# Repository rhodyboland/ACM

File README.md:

# ACM V2
**Second generation of the ACM**

This device is intended to be a control module for accessories that have been fitted to a camping/touring/4wdriving oriented vehicle. These controllable accessories could be lighting, fridge, air commpressor, water pump, tv, and more. 
The device can take inputs from various sources and use internal logic to provide monitoring to the user.
The device is to be app controlled from a mobile phone.

### Hardware:
  - 3rd generation of custom PCB with high side switches from STM. Powered by ESP32-S3
    - STM High side switches with current sensing and auto disconnect
      - 2x VNQ9025AJTR Quad Channel 30A max
      - 1x VND9008AJTR Dual Channel 67A max
  - RGB LED WS2812B
  - ESP32-S3-WROOM1-N16R8
      - USB C Programming and debug
      - Reset and boot buttons
      - Auto selecting 12v or USB 5v 3v3 regulator
  - Inputs for 2 sensors and 2 12v switches/inputs
  - Outputs Term blocks
  - High current 12V input
  - CAN for expansion

### Software:
#### Platform IO using arduino framework
  - BLE
#### Features (configurable in app)
- Switches for each channel
- Battery voltage and percentage
- Total and individual current measurement
- Auto cut-out of outputs for low battery voltage with priority selection and auto cut-in
- Power used and remaining
- Victron VE Serial input and parsing (MPPT etc.)
- JK BMS input.
- Low side switched inverter control (Highside uses standard out)
- Diagnostic outputs
- CAN to esp32 display coming

#### Custom IOS App ####

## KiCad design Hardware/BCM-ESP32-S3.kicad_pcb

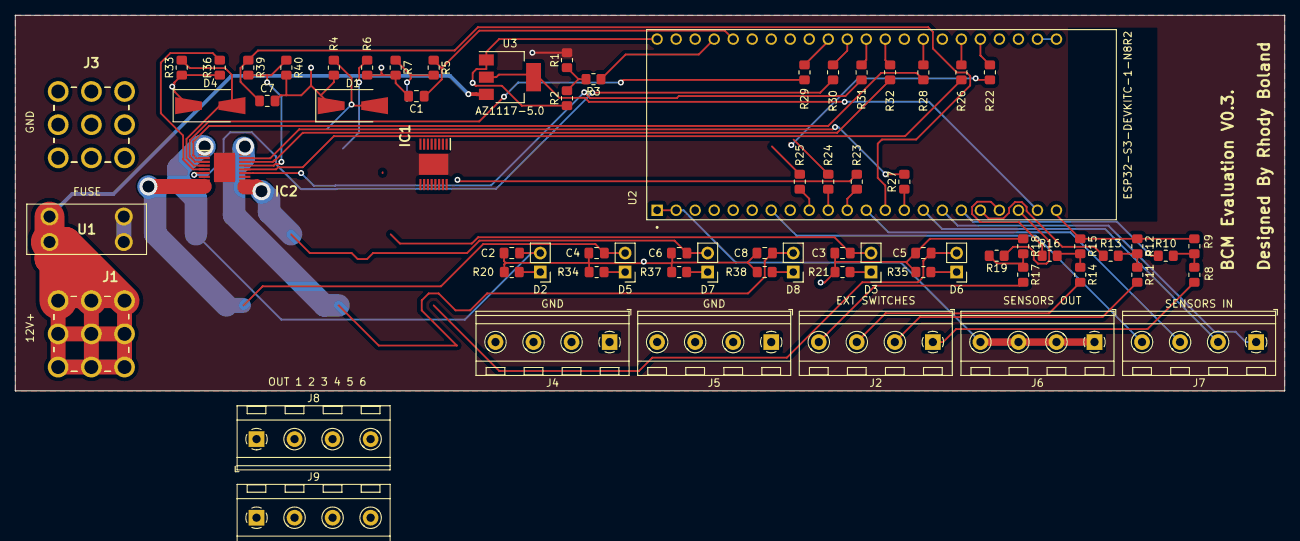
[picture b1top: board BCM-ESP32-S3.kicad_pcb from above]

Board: 2 copper layers, 169.5 x 50.2 mm, 70 parts (0 on the bottom side), 65 nets.

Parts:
C1, C2, C3, C4, C5, C6, C7, C8: 10nF; C_0805_2012Metric_Pad1.18x1.45mm_HandSolder
D1, D4: ES1DL; D_SMA-SMB_Universal_Handsoldering
D2, D3, D5, D6, D7, D8: LED; PinHeader_1x02_P2.54mm_Vertical
IC1: VND9012AJ; SOP50P600X170-17N
IC2: VNQ9080AJTR; SOP50P600X170-17N
J1: 12V+ Terminal; 74650194R
J2, J8, J9: EXT SWITCHES; TerminalBlock_RND_205-00234_1x04_P5.08mm_Horizontal
J3: GND Terminal; 74650194R
J4, J5: GND; TerminalBlock_RND_205-00234_1x04_P5.08mm_Horizontal
J6: SENSORS OUT; TerminalBlock_RND_205-00234_1x04_P5.08mm_Horizontal
J7: SENSORS IN; TerminalBlock_RND_205-00234_1x04_P5.08mm_Horizontal
R1, R5, R6, R8, R11, R14, R17, R22, R23, R24, R25, R26, R27, R28, R29, R30, R31, R32, R36, R39: 15K; R_0805_2012Metric_Pad1.20x1.40mm_HandSolder
R2, R4, R9, R12, R15, R18, R33: 4K7; R_0805_2012Metric_Pad1.20x1.40mm_HandSolder
R3, R7, R10, R13, R16, R19, R40: 1K; R_0805_2012Metric_Pad1.20x1.40mm_HandSolder
R20, R21, R34, R35, R37, R38: 2K2; R_0805_2012Metric_Pad1.20x1.40mm_HandSolder
U1: 3568
U2: ESP32-S3-DEVKITC-1-N8R2; XCVR_ESP32-S3-DEVKITC-1-N8R2
U3: AZ1117-5.0; SOT-223-3_TabPin2

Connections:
+3V3: J6.1, J6.2, J6.3, J6.4, U2.J1_1 (3V3), U2.J1_2 (3V3)
+5V: U2.J1_21 (5V0), U3.2 (VO)
+12V: IC1.17 (VCC), IC2.17 (VCC), R1.2, U1.3, U1.4
/Dual_CS: C1.1, R5.1, U2.J3_5 (GPIO2)
/Dual_INPUT0: IC1.1 (INPUT0), R25.2
/Dual_INPUT1: IC1.8 (INPUT1), R24.2
/Dual_SEL: IC1.5 (SEL), R23.2
/Dual_SEN: IC1.3 (SEn), R22.2
/EXT0: R10.1, U2.J1_17 (GPIO11)
/EXT1: R13.1, U2.J1_18 (GPIO12)
/EXT2: R16.1, U2.J1_19 (GPIO13)
/EXT3: R19.1, U2.J1_20 (GPIO14)
/EXT_SWITCH0: J2.1, R8.2
/EXT_SWITCH1: J2.2, R11.2
/EXT_SWITCH2: J2.3, R14.2
/EXT_SWITCH3: J2.4, R17.2
/OUT0: C2.1, D2.2 (A), IC2.1 (OUTPUT0), J8.1
/OUT1: C4.1, D5.2 (A), IC2.8 (OUTPUT1), J8.2
/OUT2: C6.1, D7.2 (A), IC2.9 (OUTPUT2), J8.3
/OUT3: C8.1, D8.2 (A), IC2.16 (OUTPUT3), J8.4
/OUT4: C3.1, D3.2 (A), IC1.13 (OUTPUT0), IC1.14 (OUTPUT0), IC1.15 (OUTPUT0), IC1.16 (OUTPUT0), J9.1
/OUT5: C5.1, D6.2 (A), IC1.9 (OUTPUT1), IC1.10 (OUTPUT1), IC1.11 (OUTPUT1), IC1.12 (OUTPUT1), J9.2
/Quad_CS: C7.1, R39.1, U2.J1_13 (GPIO3)
/Quad_INPUT0: IC2.3 (INPUT0), R29.2
/Quad_INPUT1: IC2.6 (INPUT1), R30.2
/Quad_INPUT2: IC2.11 (INPUT2), R31.2
/Quad_INPUT3: IC2.14 (INPUT3), R32.2
/Quad_SEL0: IC2.12 (SEL0), R26.2
/Quad_SEL1: IC2.15 (SEL1), R27.2
/Quad_SEN: IC2.2 (SEN), R28.2
/VBAT_ADC: R3.1, U2.J3_4 (GPIO1)
GND: C1.2, C2.2, C3.2, C4.2, C5.2, C6.2, C7.2, C8.2, D1.1 (K), D4.1 (K), J3.1, J3.2, J3.3, J3.4, J3.5, J3.6, J3.7, J3.8, J3.9, J4.1, J4.2, J4.3, J4.4, J5.1, J5.2, J5.3, J5.4, R2.1, R4.1, R6.1, R7.2, R9.1, R12.1, R15.1, R18.1, R20.1, R21.1, R33.1, R34.1, R35.1, R36.1, R37.1, R38.1, R40.2, U2.J1_22 (GND), U2.J3_1 (GND), U2.J3_21 (GND), U2.J3_22 (GND), U3.1 (GND)
unnamed: D1.2 (A), IC1.4 (GND), R4.2
unnamed: D2.1 (K), R20.2
unnamed: D3.1 (K), R21.2
unnamed: D4.2 (A), IC2.4 (GND), R33.2
unnamed: D5.1 (K), R34.2
unnamed: D6.1 (K), R35.2
unnamed: D7.1 (K), R37.2
unnamed: D8.1 (K), R38.2
unnamed: IC1.7 (CS), R5.2, R7.1
unnamed: IC1.2 (FaultRST), R6.2
unnamed: IC2.13 (CS), R39.2, R40.1
unnamed: IC2.5 (~FAULTRST), R36.2
unnamed: J7.1, U2.J1_16 (GPIO10)
unnamed: J7.2, U2.J1_15 (GPIO9)
unnamed: J7.3, U2.J1_12 (GPIO8)
unnamed: J7.4, U2.J1_7 (GPIO7)
unnamed: R1.1, R2.2, R3.2
unnamed: R8.1, R9.2, R10.2
unnamed: R11.1, R12.2, R13.2
unnamed: R14.1, R15.2, R16.2
unnamed: R17.1, R18.2, R19.2
unnamed: R25.1, U2.J1_9 (GPIO16)
unnamed: R24.1, U2.J1_10 (GPIO17)
unnamed: R23.1, U2.J1_11 (GPIO18)
unnamed: R22.1, U2.J3_18 (GPIO21)
unnamed: R32.1, U2.J3_13 (GPIO35)
unnamed: R31.1, U2.J3_12 (GPIO36)
unnamed: R30.1, U2.J3_11 (GPIO37)
unnamed: R29.1, U2.J3_10 (GPIO38)
unnamed: R28.1, U2.J3_15 (GPIO45)
unnamed: R27.1, U2.J1_14 (GPIO46)
unnamed: R26.1, U2.J3_17 (GPIO47)
unnamed: J1.1, J1.2, J1.3, J1.4, J1.5, J1.6, J1.7, J1.8, J1.9, U1.1, U1.2, U3.3 (VI)

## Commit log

2024-07-24 ignore update
2024-07-24 Migration to git. Add existing software and hardware files relevent to V1 (0.3).
2024-07-24 app image
2024-09-23 New code update
2024-09-26 Updates to current measurment, averages current for each channel, other minor updates
2024-10-25 New PCB photo
2025-01-11 Implement inverter control, other stability changes
2025-03-10 Include support for a temp sensor, add JK_BMS serial support
2025-03-22 Restore priority and always on channels. Also inverter control
2025-05-01 Fix victron and bms current sending. Allows negatives.
2025-05-01 Create ACMV2_LCD. Working as a proof of concept display only no data
